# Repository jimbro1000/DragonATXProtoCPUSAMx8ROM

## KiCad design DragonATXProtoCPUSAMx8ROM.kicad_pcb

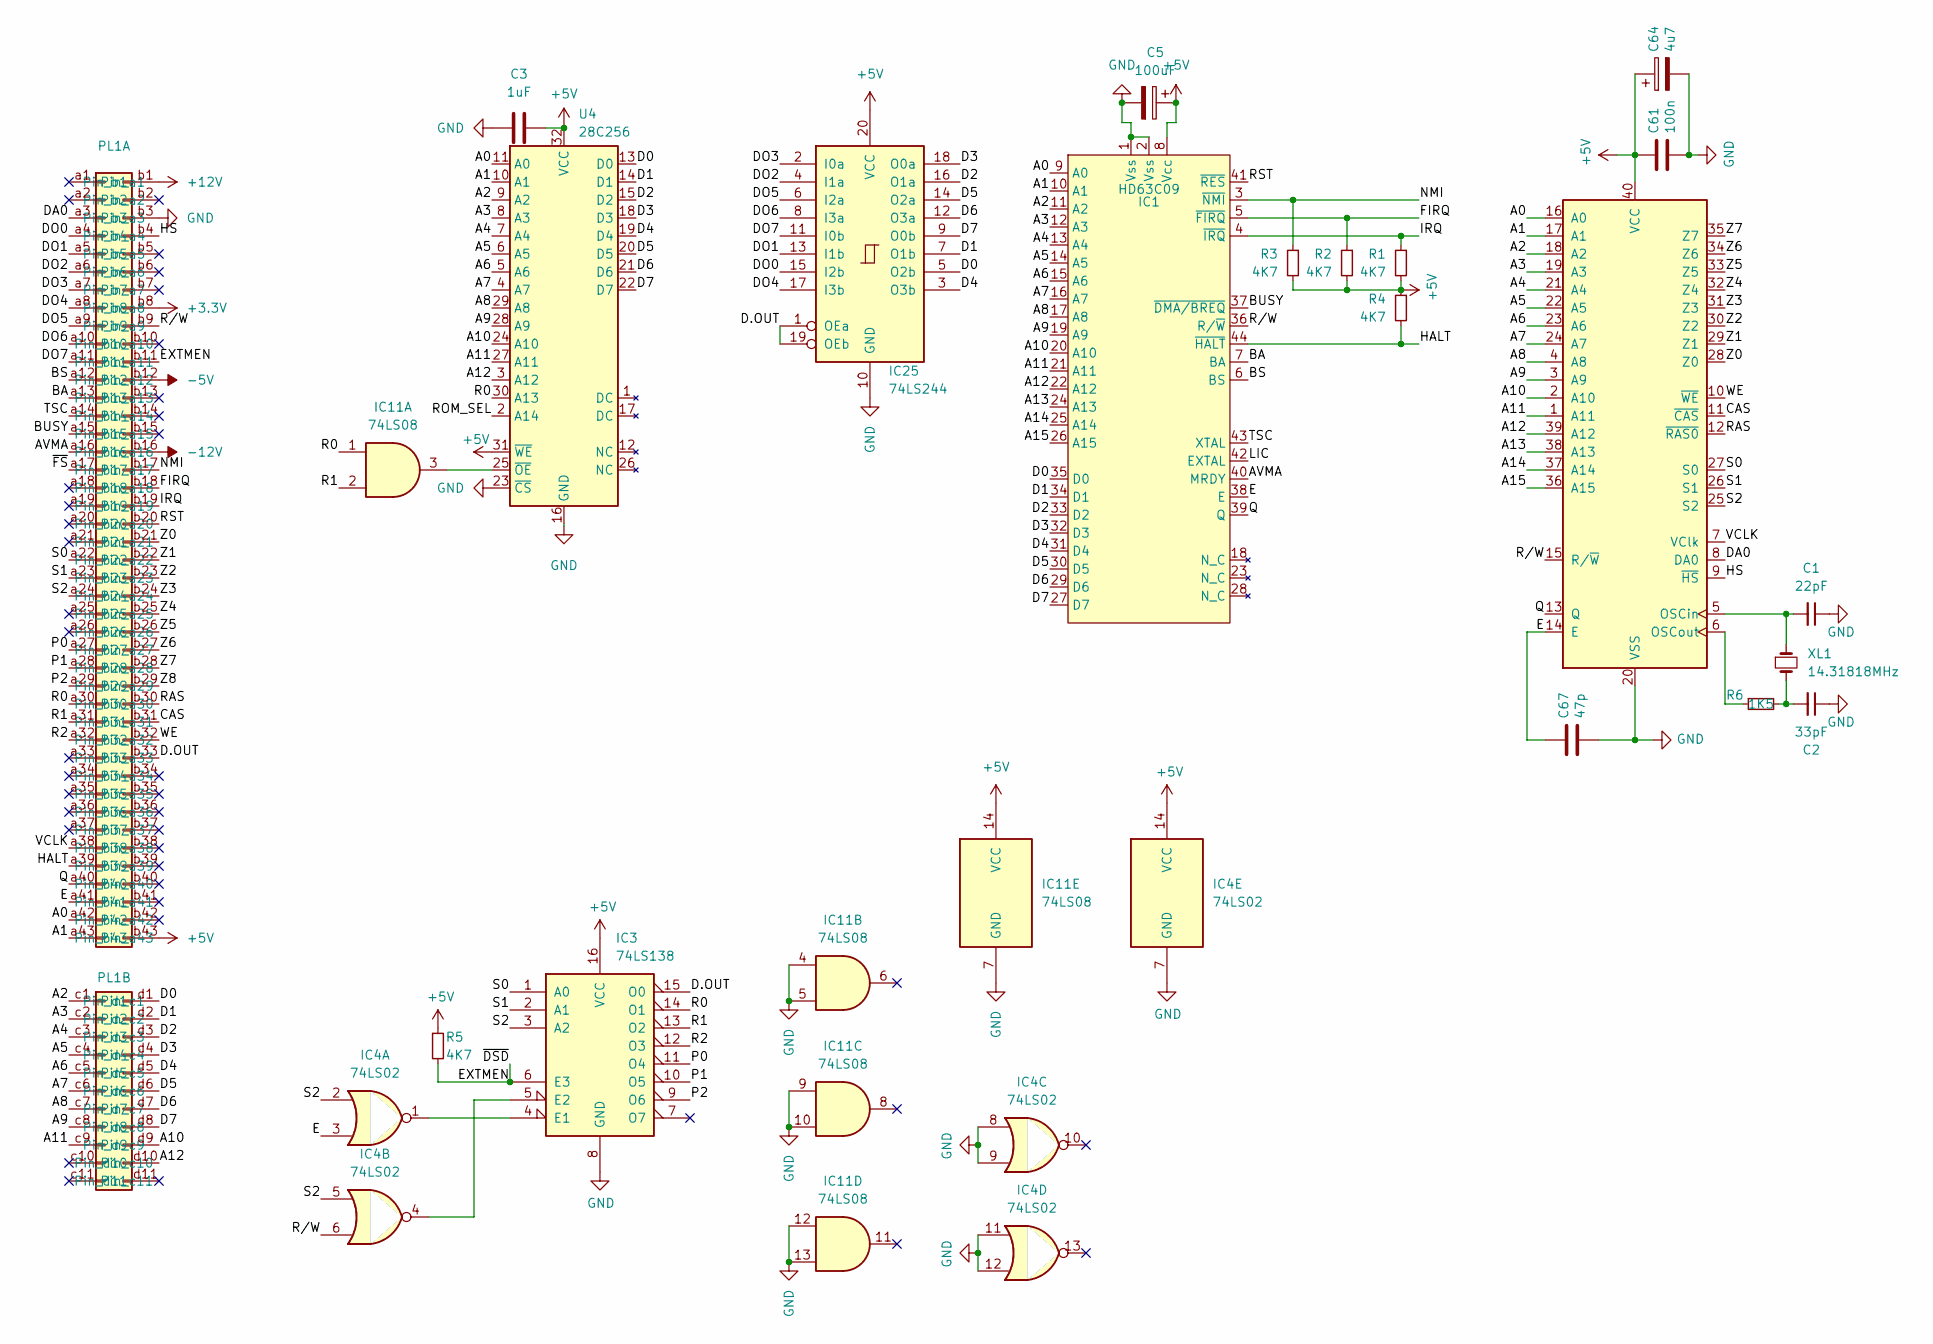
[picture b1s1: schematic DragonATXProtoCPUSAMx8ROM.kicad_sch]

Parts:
C1: 22pF; C_Disc_D3.0mm_W2.0mm_P2.50mm; DigiKey 399-13930-1-ND
C2: 33pF; C_Disc_D3.0mm_W2.0mm_P2.50mm; DigiKey BC1007CT-ND
C3: 1uF; C_Disc_D4.7mm_W2.5mm_P5.00mm
C5: 100uF; CP_Radial_D6.3mm_P2.50mm
C61: 100n; C_Disc_D6.0mm_W2.5mm_P5.00mm
C64: 4u7; CP_Radial_Tantal_D4.5mm_P2.50mm
C67: 47p; C_Disc_D6.0mm_W2.5mm_P5.00mm
IC1: HD63C09; PLCC-44_THT-Socket
IC3: 74LS138; DIP-16_W7.62mm
IC4: 74LS02; DIP-14_W7.62mm
IC11: 74LS08; DIP-14_W7.62mm
IC25: 74LS244; DIP-20_W7.62mm_Socket
IC39: 6883; DIP-40_W15.24mm_Socket
PL1: Card_Edge
R1, R2, R3, R4, R5: 4K7; R_Axial_DIN0207_L6.3mm_D2.5mm_P10.16mm_Horizontal; DigiKey CF14JT4K70CT-ND
R6: 1K5; R_Axial_DIN0207_L6.3mm_D2.5mm_P10.16mm_Horizontal; DigiKey CF14JT1K50CT-ND
U4: 28C256; PLCC-32_THT-Socket
XL1: 14.31818MHz; Crystal_HC49-U_Vertical; DigiKey CTX088-ND

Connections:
+3.3V: PL1.b8
+5V: C3.2, C5.1, C61.2, C64.1, IC1.8 (Vcc), IC3.16 (VCC), IC4.14 (VCC), IC11.14 (VCC), IC25.20 (VCC), IC39.40 (VCC), PL1.b43, R1.2, R2.2, R3.2, R4.1, R5.1, U4.31 (~WE), U4.32 (VCC)
+12V: PL1.b1
-5V: PL1.b12
-12V: PL1.b16
/A0: IC1.9 (A0), IC39.16 (A0), PL1.a42, U4.11 (A0)
/A1: IC1.10 (A1), IC39.17 (A1), PL1.a43, U4.10 (A1)
/A2: IC1.11 (A2), IC39.18 (A2), PL1.c1, U4.9 (A2)
/A3: IC1.12 (A3), IC39.19 (A3), PL1.c2, U4.8 (A3)
/A4: IC1.13 (A4), IC39.21 (A4), PL1.c3, U4.7 (A4)
/A5: IC1.14 (A5), IC39.22 (A5), PL1.c4, U4.6 (A5)
/A6: IC1.15 (A6), IC39.23 (A6), PL1.c5, U4.5 (A6)
/A7: IC1.16 (A7), IC39.24 (A7), PL1.c6, U4.4 (A7)
/A8: IC1.17 (A8), IC39.4 (A8), PL1.c7, U4.29 (A8)
/A9: IC1.19 (A9), IC39.3 (A9), PL1.c8, U4.28 (A9)
/A10: IC1.20 (A10), IC39.2 (A10), PL1.d9, U4.24 (A10)
/A11: IC1.21 (A11), IC39.1 (A11), PL1.c9, U4.27 (A11)
/A12: IC1.22 (A12), IC39.39 (A12), PL1.d10, U4.3 (A12)
/A13: IC1.24 (A13), IC39.38 (A13)
/A14: IC1.25 (A14), IC39.37 (A14)
/A15: IC1.26 (A15), IC39.36 (A15)
/AVMA: IC1.40 (MRDY), PL1.a16
/BA: IC1.7 (BA), PL1.a13
/BS: IC1.6 (BS), PL1.a12
/BUSY: IC1.37 (~DMA/BREQ), PL1.a15
/CAS: IC39.11 (~CAS), PL1.b31
/D0: IC1.35 (D0), IC25.5 (O2b), PL1.d1, U4.13 (D0)
/D1: IC1.34 (D1), IC25.7 (O1b), PL1.d2, U4.14 (D1)
/D2: IC1.33 (D2), IC25.16 (O1a), PL1.d3, U4.15 (D2)
/D3: IC1.32 (D3), IC25.18 (O0a), PL1.d4, U4.18 (D3)
/D4: IC1.31 (D4), IC25.3 (O3b), PL1.d5, U4.19 (D4)
/D5: IC1.30 (D5), IC25.14 (O2a), PL1.d6, U4.20 (D5)
/D6: IC1.29 (D6), IC25.12 (O3a), PL1.d7, U4.21 (D6)
/D7: IC1.27 (D7), IC25.9 (O0b), PL1.d8, U4.22 (D7)
/D.OUT: IC3.15 (O0), IC25.1 (OEa), IC25.19 (OEb), PL1.b33
/DA0: IC39.8 (DA0), PL1.a3
/DO0: IC25.15 (I2b), PL1.a4
/DO1: IC25.13 (I1b), PL1.a5
/DO2: IC25.4 (I1a), PL1.a6
/DO3: IC25.2 (I0a), PL1.a7
/DO4: IC25.17 (I3b), PL1.a8
/DO5: IC25.6 (I2a), PL1.a9
/DO6: IC25.8 (I3a), PL1.a10
/DO7: IC25.11 (I0b), PL1.a11
/E: C67.2, IC1.38 (E), IC4.3, IC39.14 (E), PL1.a41
/EXTMEN: IC3.6 (E3), PL1.b11, R5.2
/FIRQ: IC1.5 (~FIRQ), PL1.b18, R2.1
/HALT: IC1.44 (~HALT), PL1.a39, R4.2
/HS: IC39.9 (~HS), PL1.b4
/IRQ: IC1.4 (~IRQ), PL1.b19, R1.1
/LIC: IC1.42 (EXTAL)
/NMI: IC1.3 (~NMI), PL1.b17, R3.1
/P0: IC3.11 (O4), PL1.a27
/P1: IC3.10 (O5), PL1.a28
/P2: IC3.9 (O6), PL1.a29
/Q: IC1.39 (Q), IC39.13 (Q), PL1.a40
/R0: IC3.14 (O1), IC11.1, PL1.a30, U4.30 (A13)
/R1: IC3.13 (O2), IC11.2, PL1.a31
/R2: IC3.12 (O3), PL1.a32
/RAS: IC39.12 (~RAS0), PL1.b30
/ROM_SEL: U4.2 (A14)
/RST: IC1.41 (~RES), PL1.b20
/R/W: IC1.36 (R/~W), IC4.6, IC39.15 (R/~W), PL1.b9
/S0: IC3.1 (A0), IC39.27 (S0), PL1.a22
/S1: IC3.2 (A1), IC39.26 (S1), PL1.a23
/S2: IC3.3 (A2), IC4.2, IC4.5, IC39.25 (S2), PL1.a24
/TSC: IC1.43 (XTAL), PL1.a14
/VCLK: IC39.7 (VClk), PL1.a38
/WE: IC39.10 (~WE), PL1.b32
/Z0: IC39.28 (Z0), PL1.b21
/Z1: IC39.29 (Z1), PL1.b22
/Z2: IC39.30 (Z2), PL1.b23
/Z3: IC39.31 (Z3), PL1.b24
/Z4: IC39.32 (Z4), PL1.b25
/Z5: IC39.33 (Z5), PL1.b26
/Z6: IC39.34 (Z6), PL1.b27
/Z7: IC39.35 (Z7), PL1.b28
/Z8: PL1.b29
/~FS: PL1.a17
GND: C1.1, C2.1, C3.1, C5.2, C61.1, C64.2, C67.1, IC1.1 (Vss), IC1.2 (Vss), IC3.8 (GND), IC4.7 (GND), IC4.8, IC4.9, IC4.11, IC4.12, IC11.4, IC11.5, IC11.7 (GND), IC11.9, IC11.10, IC11.12, IC11.13, IC25.10 (GND), IC39.20 (VSS), PL1.b3, U4.16 (GND), U4.23 (~CS)
unnamed: C2.2, R6.2, XL1.2
unnamed: IC3.4 (E1), IC4.1
unnamed: IC3.5 (E2), IC4.4
unnamed: C1.2, IC39.5 (OSCin), XL1.1
unnamed: IC39.6 (OSCout), R6.1
unnamed: IC11.3, U4.25 (~OE)

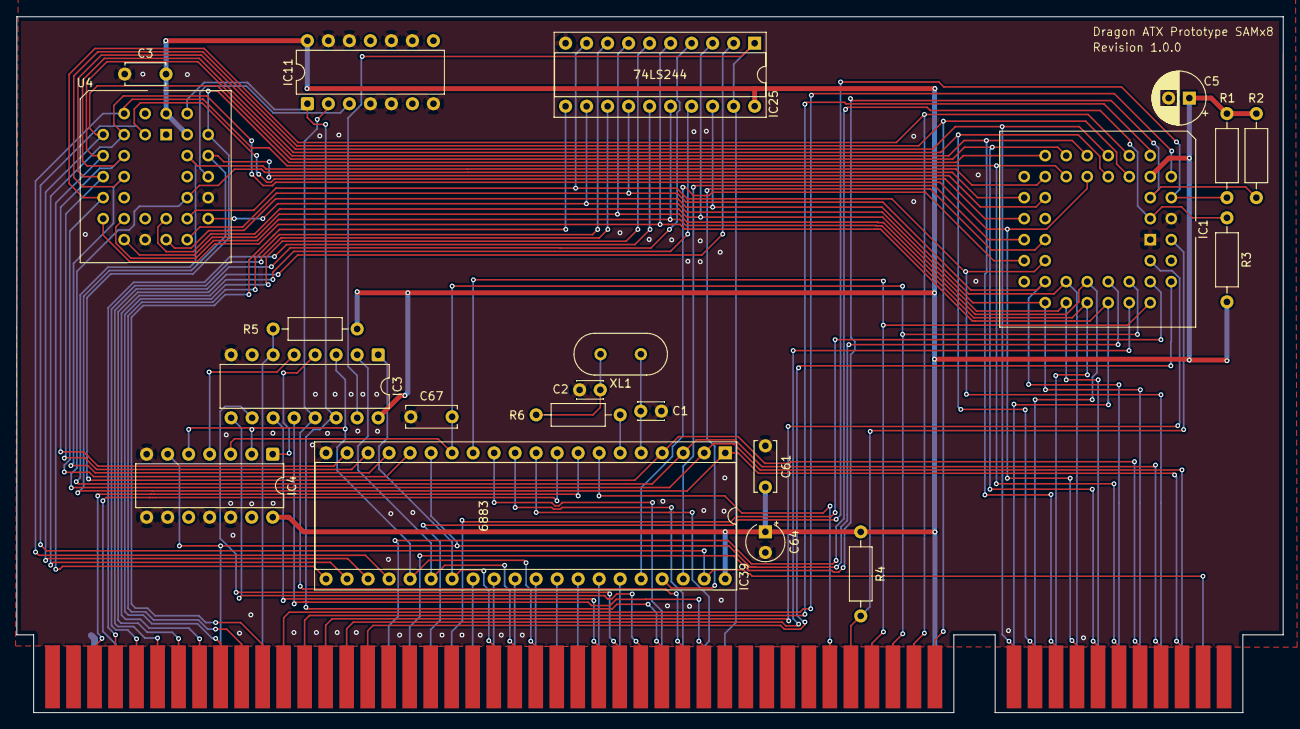
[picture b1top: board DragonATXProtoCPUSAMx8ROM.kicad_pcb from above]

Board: 2 copper layers, 153.1 x 84.1 mm, 22 parts (0 on the bottom side), 78 nets.

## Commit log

2025-05-10 wire in upper address lines for cartridge port
